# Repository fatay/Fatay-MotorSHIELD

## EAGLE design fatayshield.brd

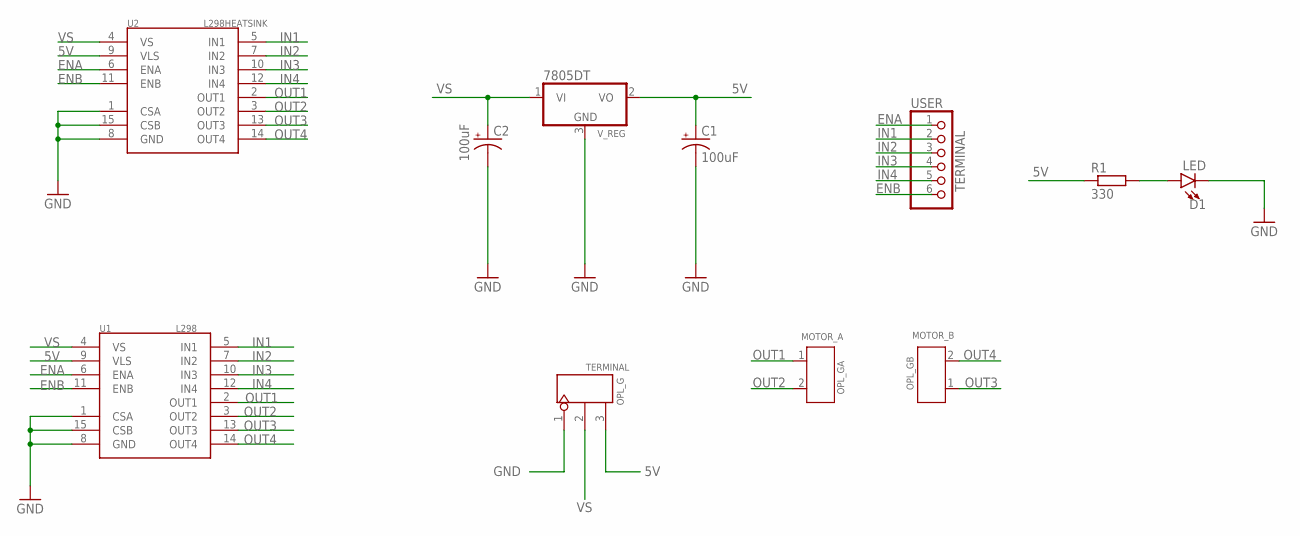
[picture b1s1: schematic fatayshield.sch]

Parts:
C1, C2: 100uF; PANASONIC_D
D1: LED; LED-0603
OPL_GA: MOTOR_A; H2-3.5-7.0X7.0MM
OPL_GB: MOTOR_B; H2-3.5-7.0X7.0MM
R1: 330; R0805
TERMINAL: OPL_G; H3-5.0-15.5X8.0MM
U1: L298; MULTIWATT15
U2: L298HEATSINK; MULTIWATT15_6400BGHEATSINK
USER: TERMINAL; 1X06-3.5MM
V_REG: 7805DT; TO252

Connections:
5V: C1.+, R1.1, TERMINAL.3, U1.9 (VLS), U2.9 (VLS), V_REG.2 (VO)
ENA: U1.6 (ENA), U2.6 (ENA), USER.1
ENB: U1.11 (ENB), U2.11 (ENB), USER.6
GND: C1.-, C2.-, D1.C, TERMINAL.1, U1.1 (CSA), U1.8 (GND), U1.15 (CSB), U2.1 (CSA), U2.8 (GND), U2.15 (CSB), V_REG.3 (GND)
IN1: U1.5 (IN1), U2.5 (IN1), USER.2
IN2: U1.7 (IN2), U2.7 (IN2), USER.3
IN3: U1.10 (IN3), U2.10 (IN3), USER.4
IN4: U1.12 (IN4), U2.12 (IN4), USER.5
unnamed: D1.A, R1.2
OUT1: OPL_GA.1, U1.2 (OUT1), U2.2 (OUT1)
OUT2: OPL_GA.2, U1.3 (OUT2), U2.3 (OUT2)
OUT3: OPL_GB.1, U1.13 (OUT3), U2.13 (OUT3)
OUT4: OPL_GB.2, U1.14 (OUT4), U2.14 (OUT4)
VS: C2.+, TERMINAL.2, U1.4 (VS), U2.4 (VS), V_REG.1 (VI)

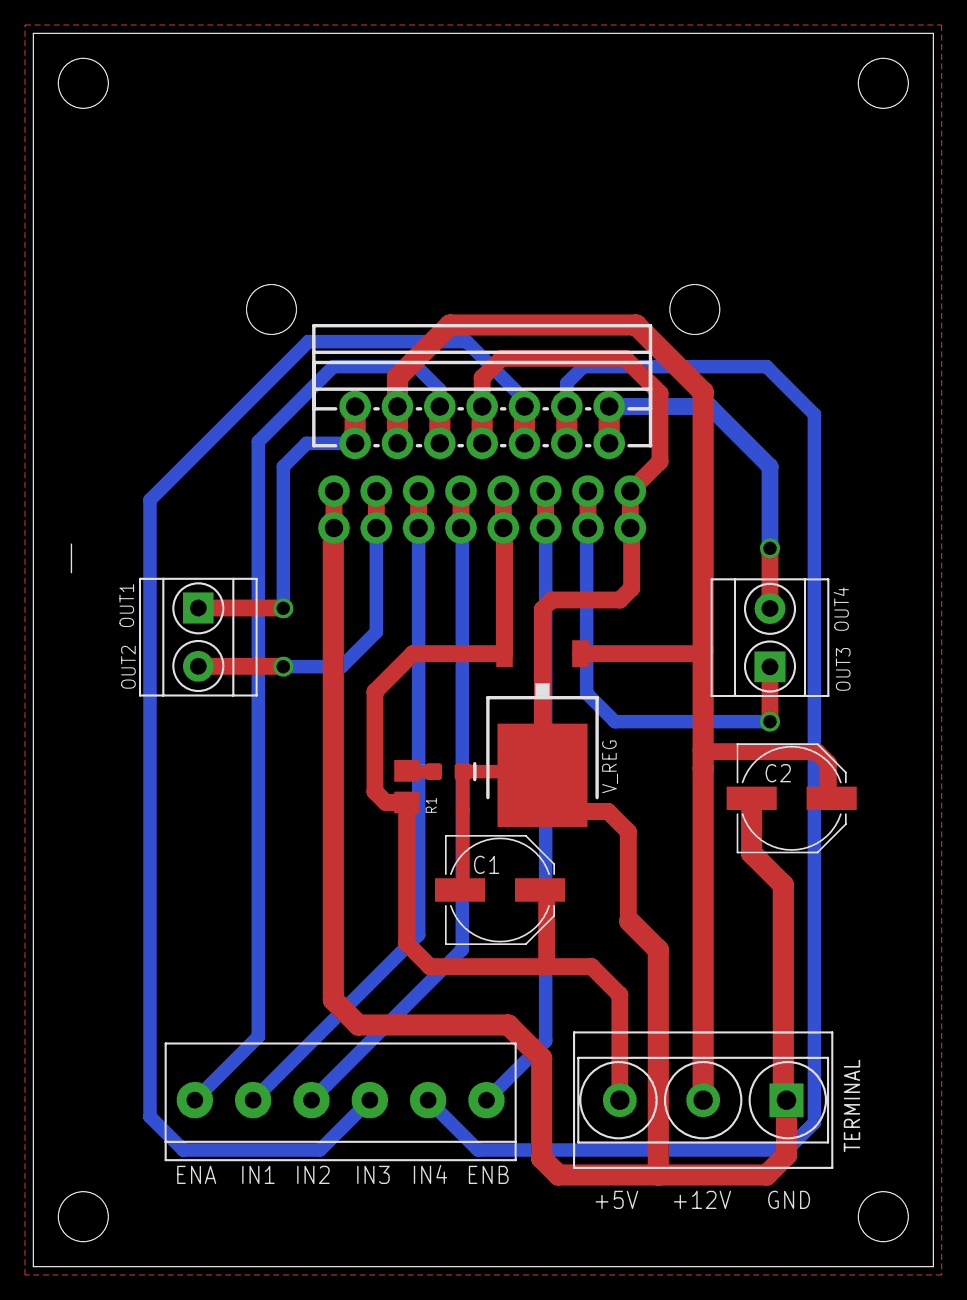
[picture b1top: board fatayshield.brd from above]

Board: 2 copper layers, 54.0 x 74.0 mm, 11 parts (0 on the bottom side), 14 nets.

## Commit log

2020-05-22 r
    r

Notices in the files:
parts and their libraries:
SparkFun-IC-Special-Function: Licensing: Creative Commons ShareAlike 4.0 International - https://creativecommons.org/licenses/by-sa/4.0
